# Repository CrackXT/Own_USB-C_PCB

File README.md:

# USB-C_PCB

PCB files for USB Power Mainboard

# Description

This board enables the installation of a USB-C connection with a voltage and current regulator connected behind it.

Like this... https://www.pololu.com/product/4083

Used to operate your microcontroller board with constant voltage and regulated current via a USB-C power supply. - To limit over-voltage and over-current and prevent damage. 

The board can be produced here (AISLER) with the files (.brd and .sch) or by any other PCB manufacturer. -> https://aisler.net/

# Spec
Vin:  2,8 - 22V<br>
Vout: 5V (typ., min.4,85V, max.5,15V)<br>
Iout: 1A

# Serie

- .pro

# Layout

Top<br>

Bottom<br>

Routing/Dimensions(inch)<br>

Schematic<br>
Schematic as .pdf at the top of the page.

# License

Open hardware, use it, mod it, whatever you want, feel free...

# Thanks!

Own design and layout.

# Version - Build

v4.0 - 07.05.2023

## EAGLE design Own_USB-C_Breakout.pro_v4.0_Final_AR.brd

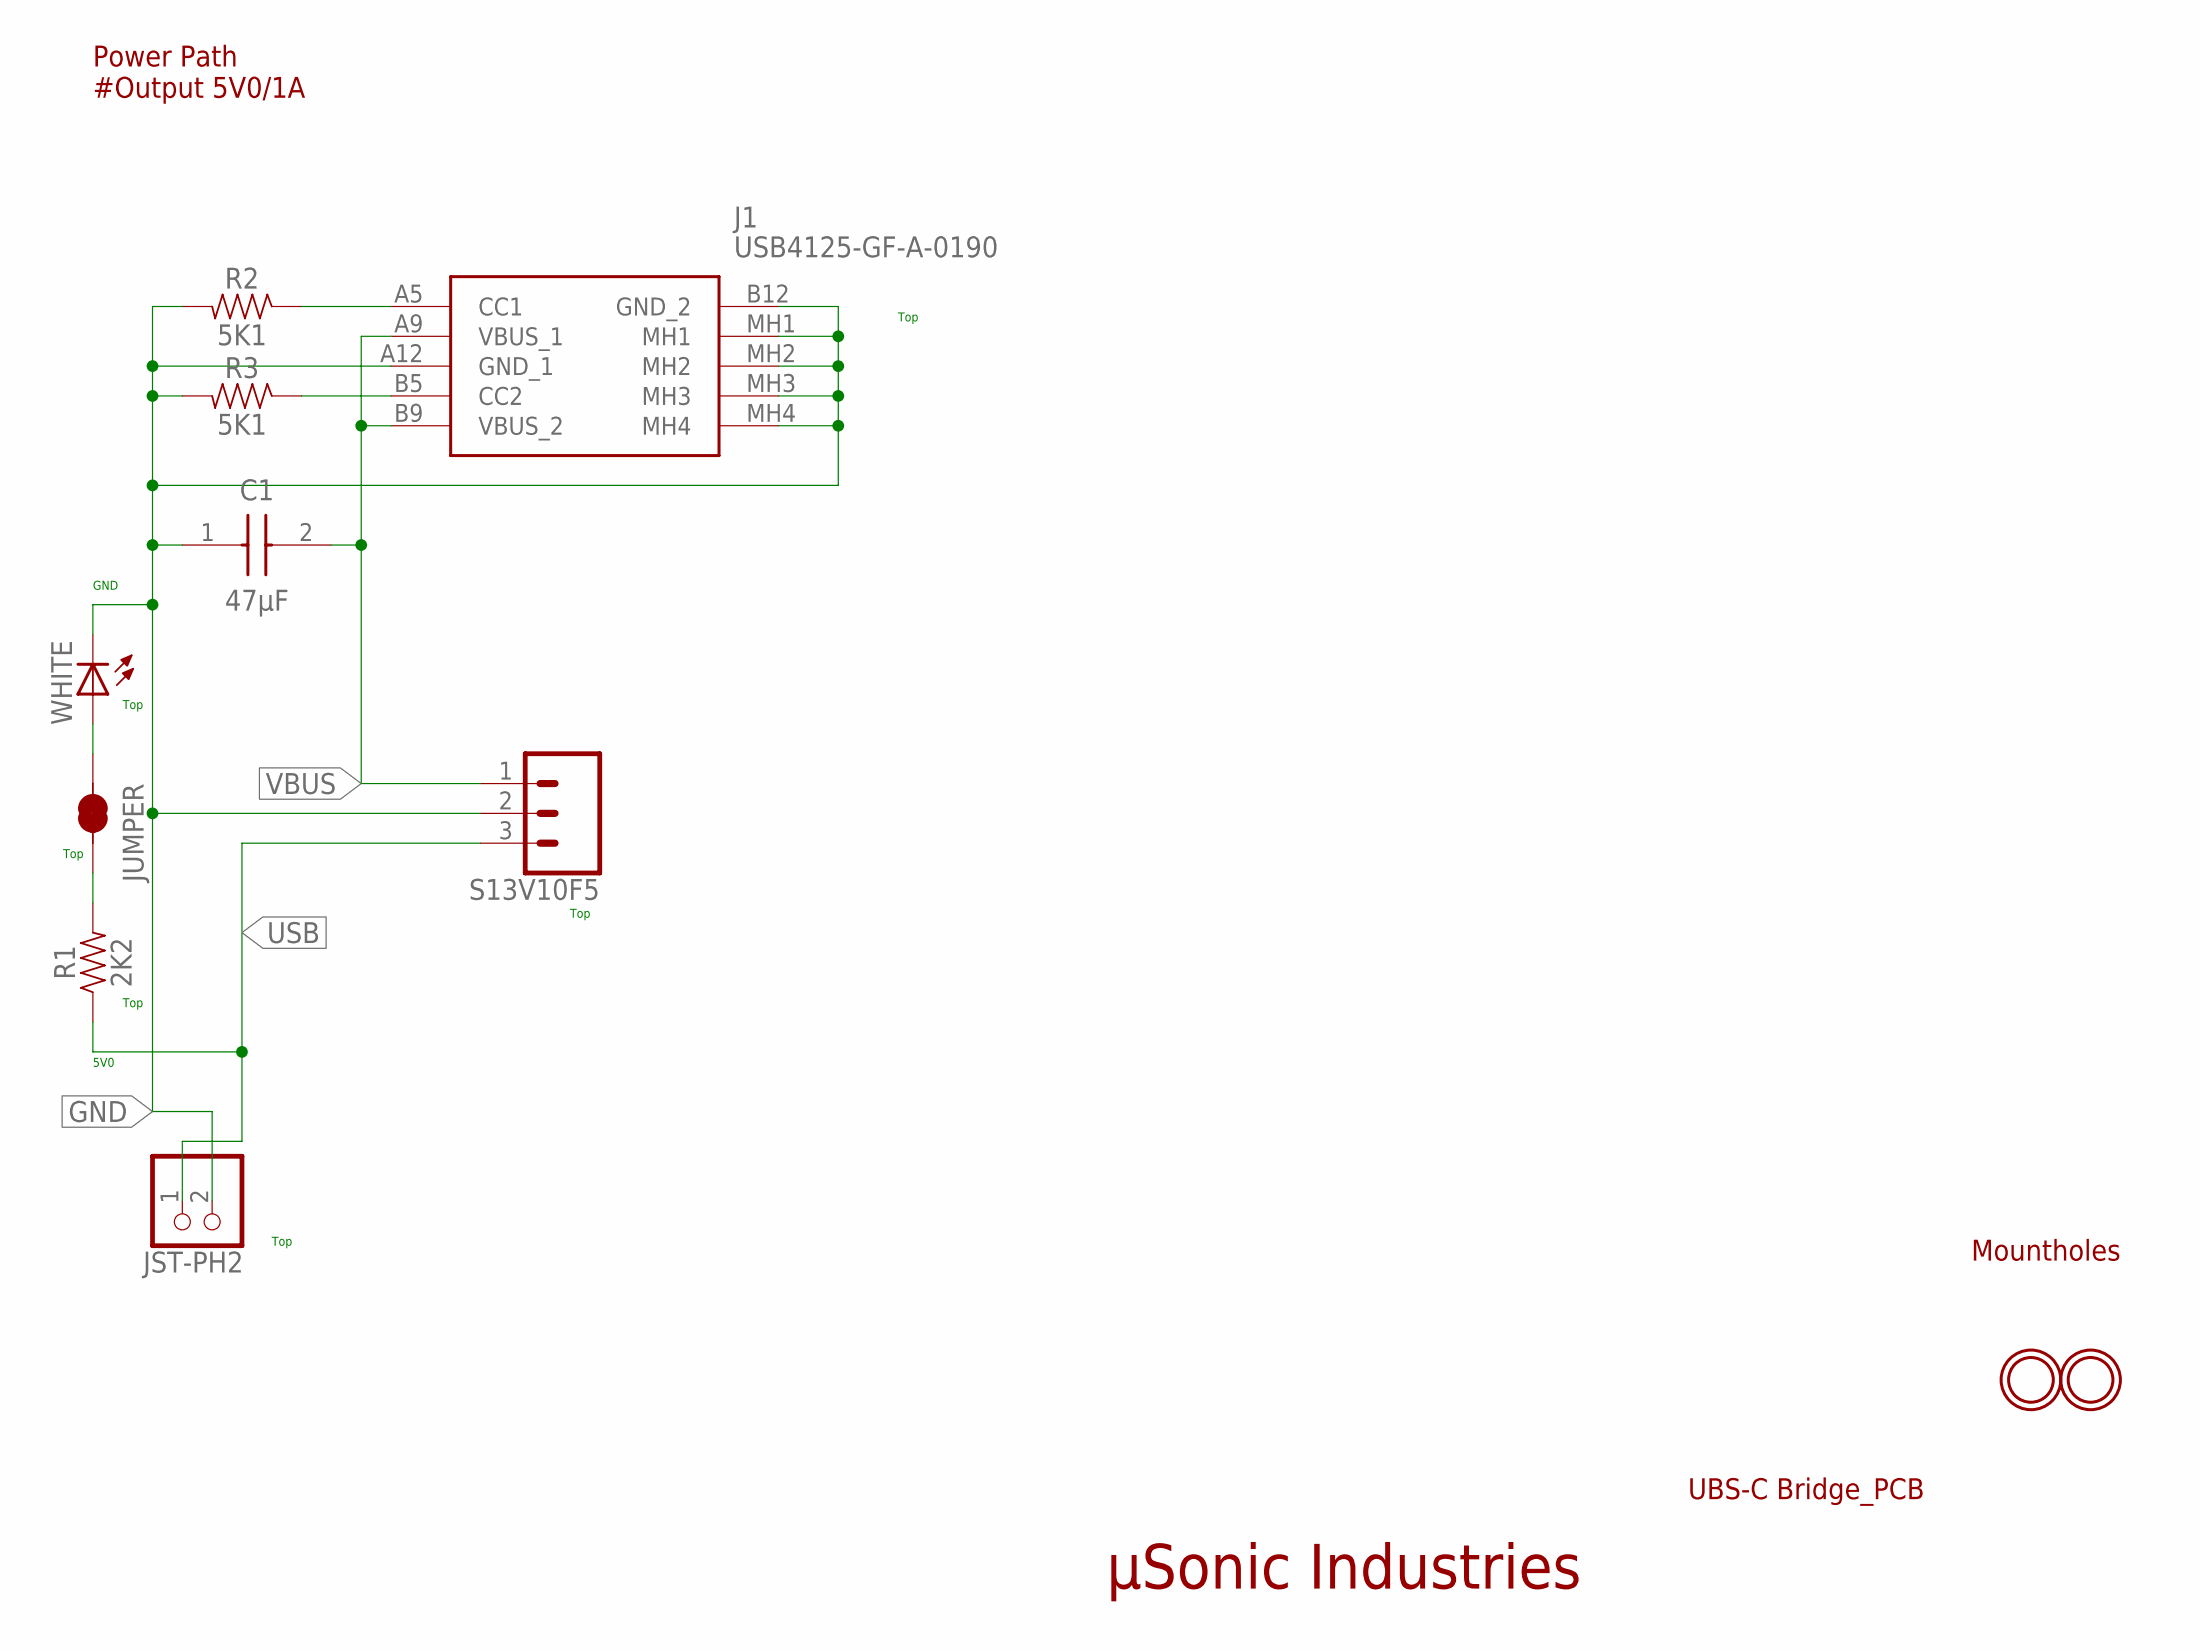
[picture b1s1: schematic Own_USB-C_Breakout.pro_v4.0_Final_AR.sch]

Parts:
C1: 47µF; CAPC5750X310N
J1: USB4125-GF-A-0190; USB4125GFA0190
JST-PH2: JST_2PINOWN; JST-PH-2-THMOWN
JUMPER: JUMPER-SMT_2_NC_TRACE_SILK; SMT-JUMPER_2_NC_TRACE_SILK
R1: 2K2; 0805
R2, R3: 5K1; 0805
S13V10F5: CONN_031X03_NO_SILK; 1X03_NO_SILK
U$1, U$2: MOUNTINGHOLE2.5; MOUNTINGHOLE_2.5_PLATED
WHITE: LEDCHIPLED_0805; CHIPLED_0805

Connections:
GND: C1.1, J1.A12 (GND_1), J1.B12 (GND_2), J1.MH1, J1.MH2, J1.MH3, J1.MH4, JST-PH2.2 (1), R2.2, R3.2, S13V10F5.2, WHITE.C
JUMPER1: JUMPER.1, WHITE.A
JUMPER2: JUMPER.2, R1.2
unnamed: J1.B5 (CC2), R3.1
unnamed: J1.A5 (CC1), R2.1
USB: JST-PH2.1 (2), R1.1, S13V10F5.3
VBUS: C1.2, J1.A9 (VBUS_1), J1.B9 (VBUS_2), S13V10F5.1

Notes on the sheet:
µSonic Industries
UBS-C Bridge_PCB
Power Path #Output 5V0/1A
Top
Mountholes
GND
5V0

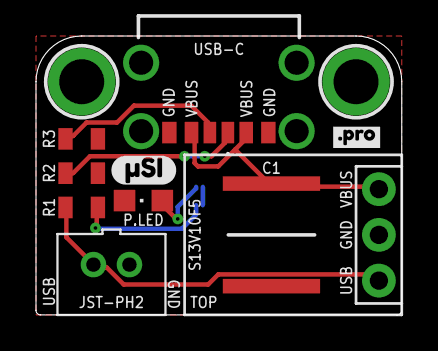
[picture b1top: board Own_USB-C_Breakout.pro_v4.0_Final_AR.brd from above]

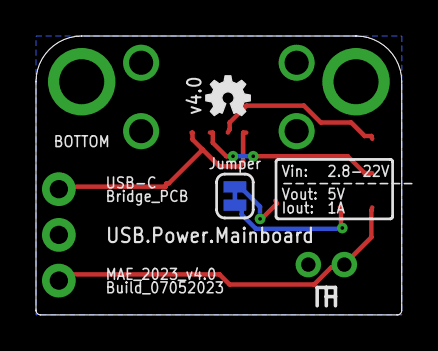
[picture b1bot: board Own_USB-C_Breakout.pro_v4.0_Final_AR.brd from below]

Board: 2 copper layers, 20.3 x 15.5 mm, 14 parts (2 on the bottom side), 7 nets.

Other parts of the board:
U$4: PRO2
U$6: OSHW-LOGO-MINI
U$7: µSI2

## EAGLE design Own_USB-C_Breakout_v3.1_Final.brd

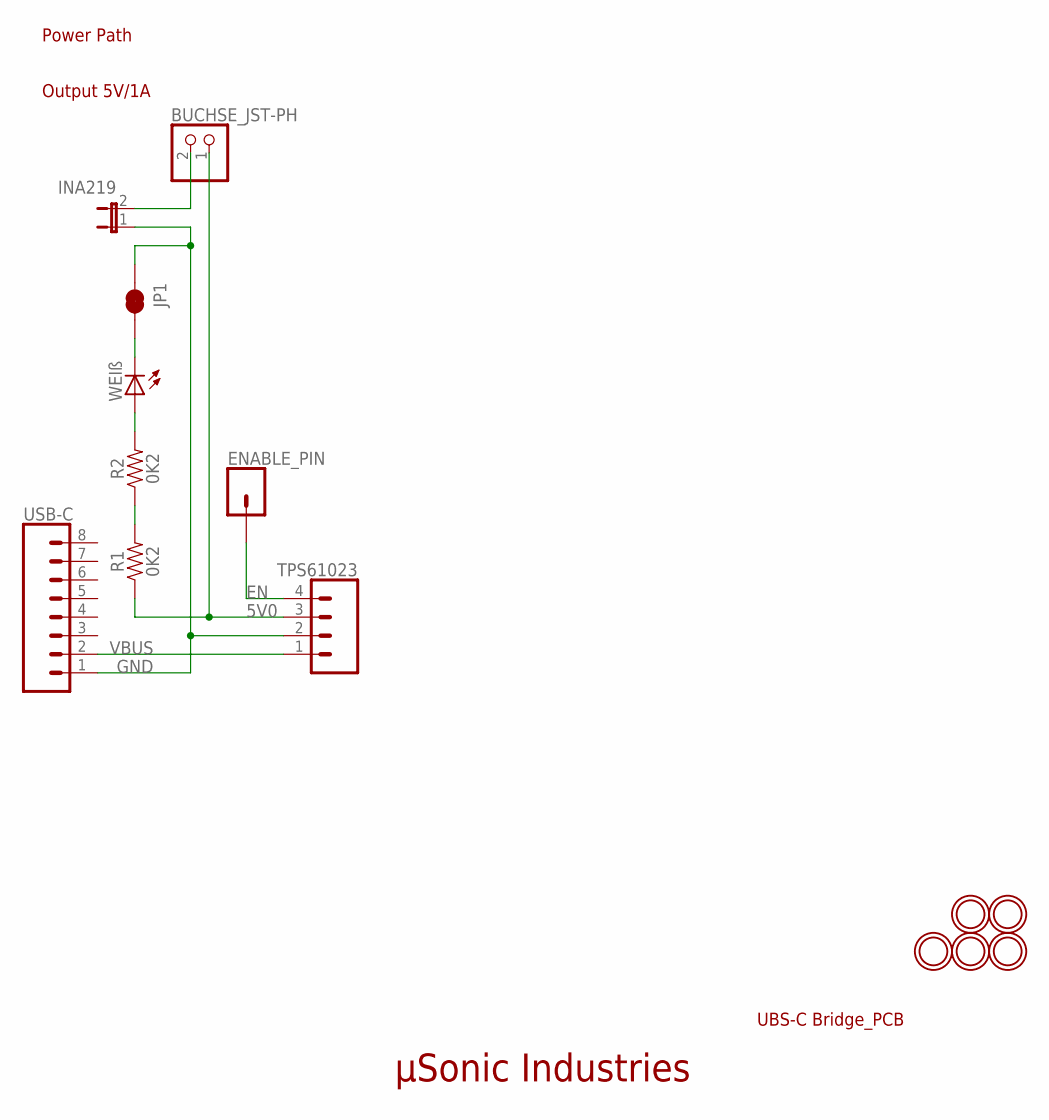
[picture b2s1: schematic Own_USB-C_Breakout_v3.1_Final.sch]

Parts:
BUCHSE_JST-PH: JST_2PINOWN; JST-PH-2-THMOWN
ENABLE_PIN: CONN_01PTH_NO_SILK_YES_STOP; 1X01_NO_SILK
INA219: JP1E; JP1
JP1: JUMPER-SMT_2_NC_TRACE_SILK; SMT-JUMPER_2_NC_TRACE_SILK
R1, R2: 0K2; 0805
TPS61023: CONN_041X04_NO_SILK; 1X04_NO_SILK
U$1, U$2, U$10, U$11, U$14: MOUNTINGHOLE2.5; MOUNTINGHOLE_2.5_PLATED
USB-C: CONN_08NO_SILK_FEMALE_PTH; 1X08_NO_SILK
WEIß: LEDCHIPLED_0805; CHIPLED_0805

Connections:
5V: R2.2, WEIß.A
5V0: BUCHSE_JST-PH.1 (2), R1.1, TPS61023.3
EN: ENABLE_PIN.1, TPS61023.4
GND: INA219.1, JP1.1, TPS61023.2, USB-C.1
GND_JST: BUCHSE_JST-PH.2 (1), INA219.2
unnamed: JP1.2, WEIß.C
unnamed: R1.2, R2.1
VBUS: TPS61023.1, USB-C.2

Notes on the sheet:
µSonic Industries
UBS-C Bridge_PCB
Power Path
Output 5V/1A

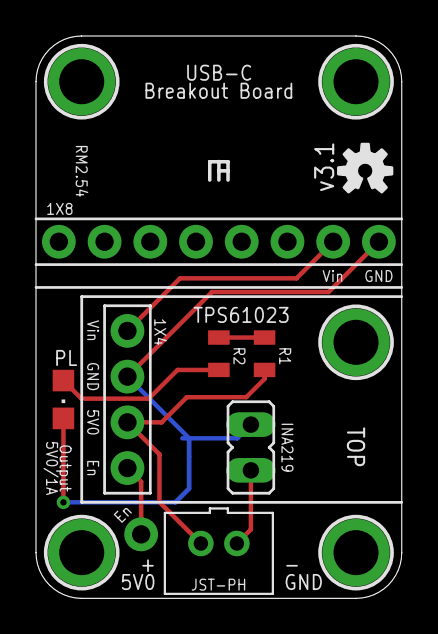
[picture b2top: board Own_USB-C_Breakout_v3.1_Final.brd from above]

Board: 2 copper layers, 20.3 x 31.2 mm, 15 parts (1 on the bottom side), 8 nets.

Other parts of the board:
U$4: OSHW-LOGO-S

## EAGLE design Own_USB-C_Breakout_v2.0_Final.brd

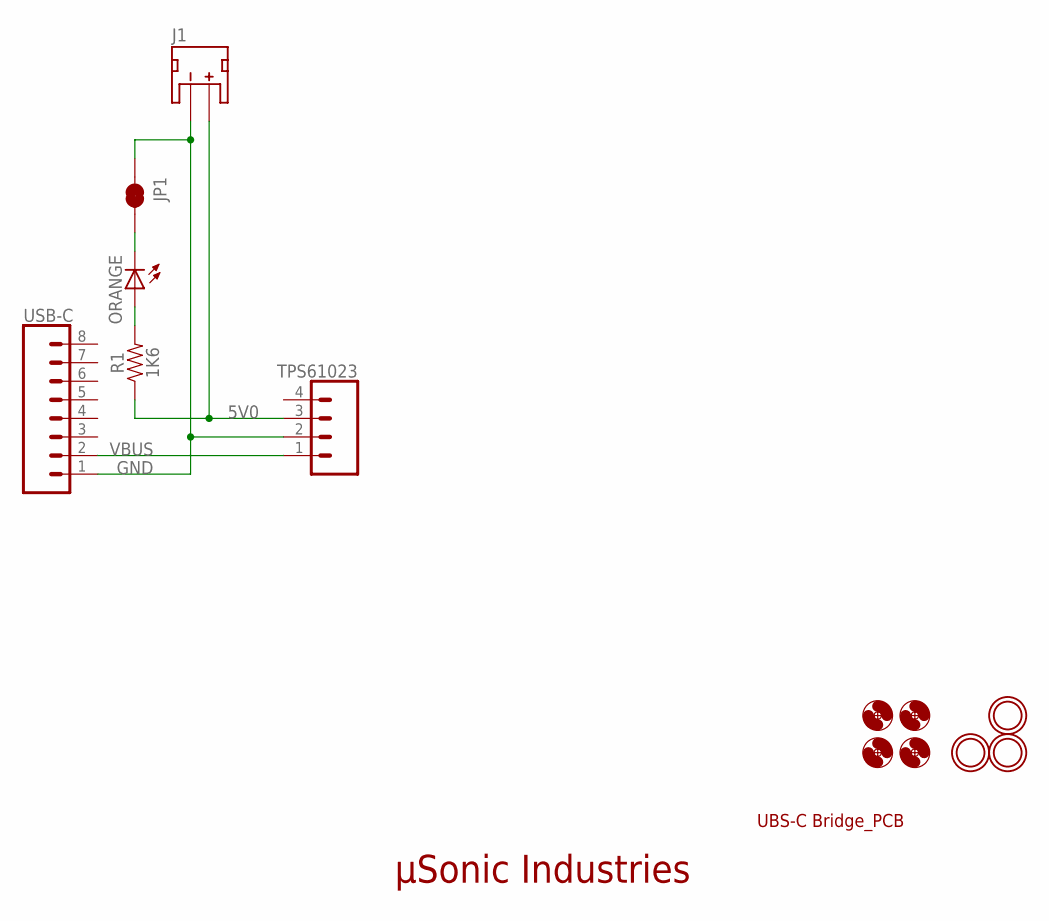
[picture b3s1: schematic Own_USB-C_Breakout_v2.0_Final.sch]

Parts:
J1: JST_2MM_MALE; JST-2-SMD
JP1: JUMPER-SMT_2_NC_TRACE_SILK; SMT-JUMPER_2_NC_TRACE_SILK
ORANGE: LEDCHIPLED_0603; CHIPLED_0603
R1: 1K6; 0805
TPS61023: CONN_041X04_NO_SILK; 1X04_NO_SILK
U$1, U$2, U$14: MOUNTINGHOLE2.5; MOUNTINGHOLE_2.5_PLATED
U$5, U$6, U$7, U$8: MOUNTHOLEBIG; OWN_MOUNTHOLE_BIGAREA
USB-C: CONN_08NO_SILK_FEMALE_PTH; 1X08_NO_SILK

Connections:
5V: ORANGE.A, R1.2
5V0: J1.2 (+), R1.1, TPS61023.3
GND: J1.1 (-), JP1.1, TPS61023.2, USB-C.1
unnamed: JP1.2, ORANGE.C
VBUS: TPS61023.1, USB-C.2

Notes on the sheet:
µSonic Industries
UBS-C Bridge_PCB

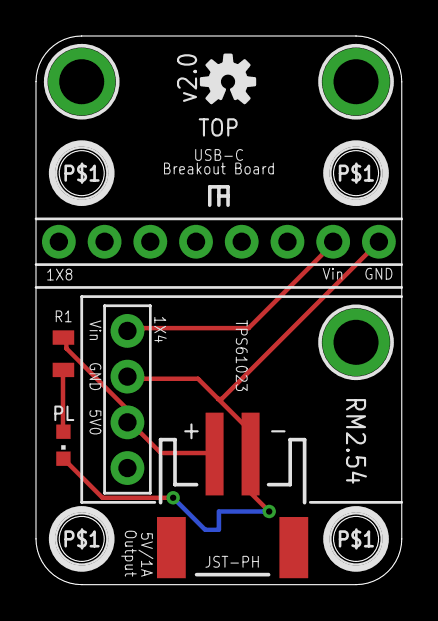
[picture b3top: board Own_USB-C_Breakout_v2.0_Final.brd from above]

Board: 2 copper layers, 20.3 x 30.5 mm, 14 parts (1 on the bottom side), 5 nets.

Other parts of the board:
U$4: OSHW-LOGO-S

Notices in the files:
parts and their libraries:
microbuilder: This work is placed in the public domain, and may be freely used for commercial and non-commercial work with the following conditions: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
SparkFun-Aesthetics: Licensing: Creative Commons ShareAlike 4.0 International - https://creativecommons.org/licenses/by-sa/4.0
